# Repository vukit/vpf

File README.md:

# Уличная кормушка для собак крупных пород

Надежная автоматизированная система кормления, спроектированная специально для крупных пород собак и эксплуатации в открытых вольерах. Проект успешно прошел проверку реальными условиями (снег, дождь, жара) и находится в эксплуатации с 2024 года.

## Ключевые особенности

*   **Компактный механизм:** Вместо громоздкого шнека использован оригинальный узел с пропеллером, что позволило существенно уменьшить габариты корпуса без потери производительности.
*   **Всепогодность:** Кормушка предназначена для установки на открытых площадках. Не требует навеса, дополнительной защиты или регулярной чистки механизма.
*   **Безопасность (5В):** Устройство питается от напряжения 5 вольт. Это гарантирует полную электрическую безопасность для питомца даже в случае повреждения кабеля.
*   **Автономность и объем:** Резервуар вмещает до 3.5 кг корма, чего достаточно для обеспечения собаки едой в течение 7 дней.
*   **Умная логика выдачи:** При временном отключении питания устройство автоматически «догоняет» график, выдавая пропущенные порции сразу после возобновления работы.

## Технические характеристики

*   **Точность дозирования:** ±20 грамм (порции задаются в граммах).
*   **График кормления:** До 3-х сессий в сутки в заданное время.
*   **Управление:** Мобильное приложение (связь через BLE).
*   **Функции приложения:** 
    *   Настройка расписания.
    *   Выдача порции вне очереди по команде.
    *   Обновление прошивки (OTA firmware update).

## Аппаратная часть
* **Микроконтроллер:** ESP32-C3.
* **Двигатель:** Bringsmart JS-50B(S) BLDC, DC 5V, CW/CCW, 2rpm, 10kgf/cm².
* **RTC:** Модуль DS3231 I2C.
* **Измерение веса:** TZT HX711 весовой модуль, 4 датчика FGHGF 34X34mm 5kg.
* **Питание:** 5В.

## Программное обеспечение
* **Язык:** firmware - C (ESP-IDF, FreeRTOS), приложение - Java (Android Studio).

## Опыт эксплуатации
Кормушка работает на открытом воздухе более 2-х лет, не требуя специального укрытия или частого технического обслуживания. Конструкция доказала свою устойчивость к обледенению и забиванию механизмов.

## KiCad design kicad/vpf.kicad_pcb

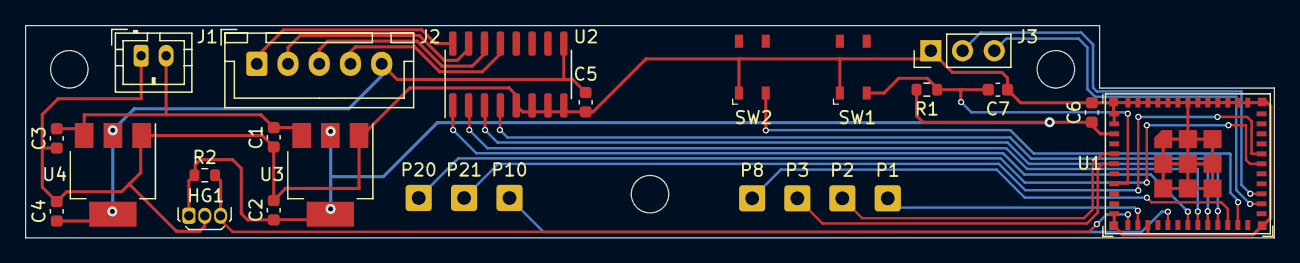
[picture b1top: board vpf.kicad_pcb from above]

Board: 2 copper layers, 100.0 x 17.0 mm, 26 parts (0 on the bottom side), 24 nets.

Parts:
C1, C2, C3, C4: 22uF/16V(10%); C_0603_1608Metric
C5, C6: 0.1uF/16V(10%); C_0603_1608Metric
C7: 1uF/16V(10%); C_0603_1608Metric
HG1: SS451A; TO-92Flat
J1: Conn_01x02_Pin; JST_PH_B2B-PH-K_1x02_P2.00mm_Vertical
J2: Conn_01x05_Pin; JST_XH_B5B-XH-A_1x05_P2.50mm_Vertical
J3: Conn_01x03_Pin; PinHeader_1x03_P2.54mm_Vertical
P1, P2, P3, P8, P10, P20, P21: Conn_01x01; SolderWire-0.5sqmm_1x01_D0.9mm_OD2.1mm
R1: 10k(1%); R_0603_1608Metric
R2: 6.8k(1%); R_0603_1608Metric
SW1, SW2: PTS810SJM250SMTRLFS; SW_PUSH_4
U1: ESP32-C3-MINI-1
U2: ULN2003A; SOIC-16_3.9x9.9mm_P1.27mm
U3: LD1117S33CTR; SOT-223
U4: LD1117S50CTR; SOT-223

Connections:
+3.3V: C2.1, C6.1, HG1.1 (U1), R1.1, R2.1, U1.3 (3V3), U3.2 (VOUT), U3.4 (VOUT)
+5V: C4.1, C5.1, J2.5, U2.9 (COM), U4.2 (VOUT), U4.4 (VOUT)
+12V: C1.1, C3.1, J1.2, U3.3 (VIN), U4.3 (VIN)
/GPI09: SW2.3, U1.23 (GPIO9)
GND: C1.2, C2.2, C3.2, C4.2, C5.2, C6.2, C7.2, HG1.2 (U2), J1.1, J3.1, SW1.1, SW2.1, U1.1 (GND), U1.2 (GND), U1.11 (GND), U1.14 (GND), U1.36 (GND), U1.37 (GND), U1.38 (GND), U1.39 (GND), U1.40 (GND), U1.41 (GND), U1.42 (GND), U1.43 (GND), U1.44 (GND), U1.45 (GND), U1.46 (GND), U1.47 (GND), U1.48 (GND), U1.49 (GND), U1.50 (GND), U1.51 (GND), U1.52 (GND), U1.53 (GND), U2.5 (I5), U2.6 (I6), U2.7 (I7), U2.8 (GND), U3.1 (GND), U4.1 (GND)
unnamed: HG1.3 (UH1), R2.2, U1.12 (GPIO0/ADC1_CH0/XTAL_32K_P)
unnamed: J2.1, U2.16 (O1)
unnamed: J2.2, U2.15 (O2)
unnamed: J2.3, U2.14 (O3)
unnamed: J2.4, U2.13 (O4)
unnamed: J3.2, U1.27 (GPIO19/USB_D+)
unnamed: J3.3, U1.26 (GPIO18/USB_D-)
unnamed: P1.1, U1.13 (GPIO1/ADC1_CH1/XTAL_32K_N)
unnamed: P2.1, U1.5 (GPIO2/ADC1_CH2)
unnamed: P3.1, U1.6 (GPIO3/ADC1_CH3)
unnamed: P8.1, U1.22 (GPIO8)
unnamed: P10.1, U1.16 (GPIO10)
unnamed: P20.1, U1.30 (GPIO20/U0RXD)
unnamed: P21.1, U1.31 (GPIO21/U0TXD)
unnamed: C7.1, R1.2, SW1.3, U1.8 (EN/CHIP_PU)
unnamed: U1.18 (GPIO4/ADC1_CH4), U2.1 (I1)
unnamed: U1.19 (GPIO5/ADC2_CH0), U2.2 (I2)
unnamed: U1.20 (GPIO6), U2.3 (I3)
unnamed: U1.21 (GPIO7), U2.4 (I4)

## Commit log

2026-04-05 Release v1.0.0 commit
